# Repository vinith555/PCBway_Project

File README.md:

Custom PCB Badge for PCBWay Competition
Description
This badge PCB was designed for PCBWay’s competition, showcasing their precision in PCB manufacturing. It features integrated LEDs in a custom shape, making it ideal for use at events or as promotional giveaways. The badge is compact, durable, and powered by a battery or USB for easy use.

Features
Creative custom-shaped design
Integrated LEDs for visual appeal
Powered by a battery or USB for portability
Made from durable FR4 PCB material
Suitable for events, branding, or giveaways
Components
Material: FR4 PCB
LEDs: [Number of LEDs]
Power Source: Battery/USB
Other Components: Resistors, capacitors, etc.
PCB Specifications
Dimensions: [Specify dimensions]
Surface Finish: [e.g., HASL, ENIG]
Solder Mask Color: [e.g., Green, Red]
Layers: [Number of layers]
Getting Started
Requirements
Soldering tools
Battery or USB for power
Assembly Instructions
Solder the components (LEDs, resistors, etc.) to the PCB.
Connect the battery or USB power source.
Test the badge to ensure all components, especially the LEDs, are functioning properly.
Project Files
Gerber Files: [Provide link]
BOM: [Provide link]
Schematics: [Provide link]
License
Licensed under the [Insert License] License.

Contributing
Contributions are welcome! Submit pull requests or suggest improvements via the repository.

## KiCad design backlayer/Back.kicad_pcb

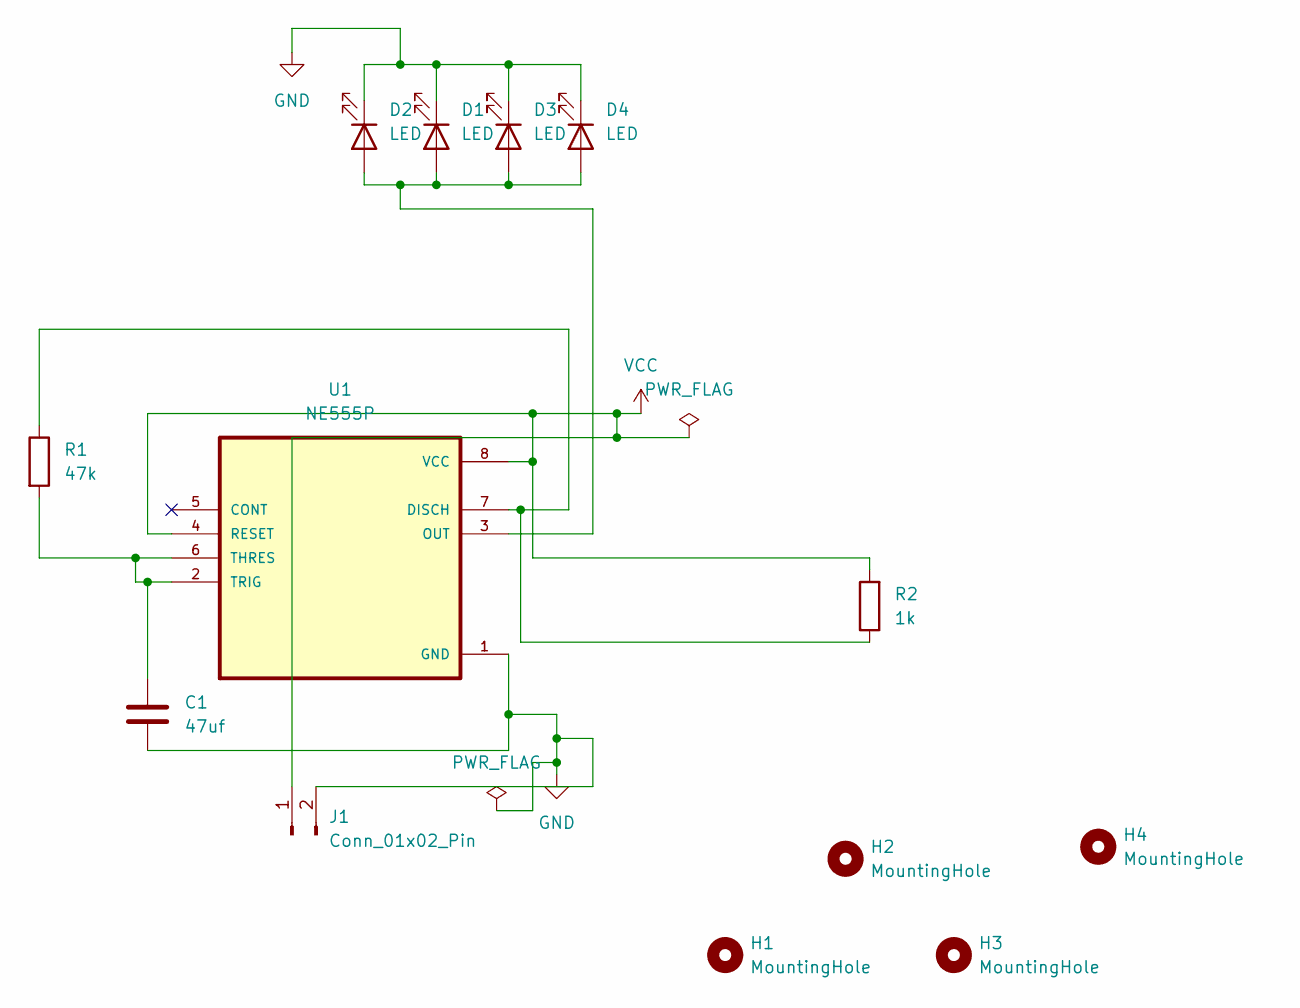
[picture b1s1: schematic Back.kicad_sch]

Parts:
C1: 47uf; CP_Radial_D12.5mm_P5.00mm
D1, D2, D3, D4: LED; LED_D3.0mm
H1, H2, H3, H4: MountingHole; MountingHole_2.5mm
J1: Conn_01x02_Pin; PinHeader_1x02_P2.54mm_Vertical
R1: 47k; R_Axial_DIN0207_L6.3mm_D2.5mm_P10.16mm_Horizontal
R2: 1k; R_Axial_DIN0207_L6.3mm_D2.5mm_P10.16mm_Horizontal
U1: NE555P; DIP794W45P254L959H508Q8

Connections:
GND: C1.2, D1.1 (K), D2.1 (K), D3.1 (K), D4.1 (K), J1.2, U1.1 (GND)
unnamed: D1.2 (A), D2.2 (A), D3.2 (A), D4.2 (A), U1.3 (OUT)
unnamed: R1.1, R2.1, U1.7 (DISCH)
unnamed: C1.1, R1.2, U1.2 (TRIG), U1.6 (THRES)
VCC: J1.1, R2.2, U1.4 (RESET), U1.8 (VCC)

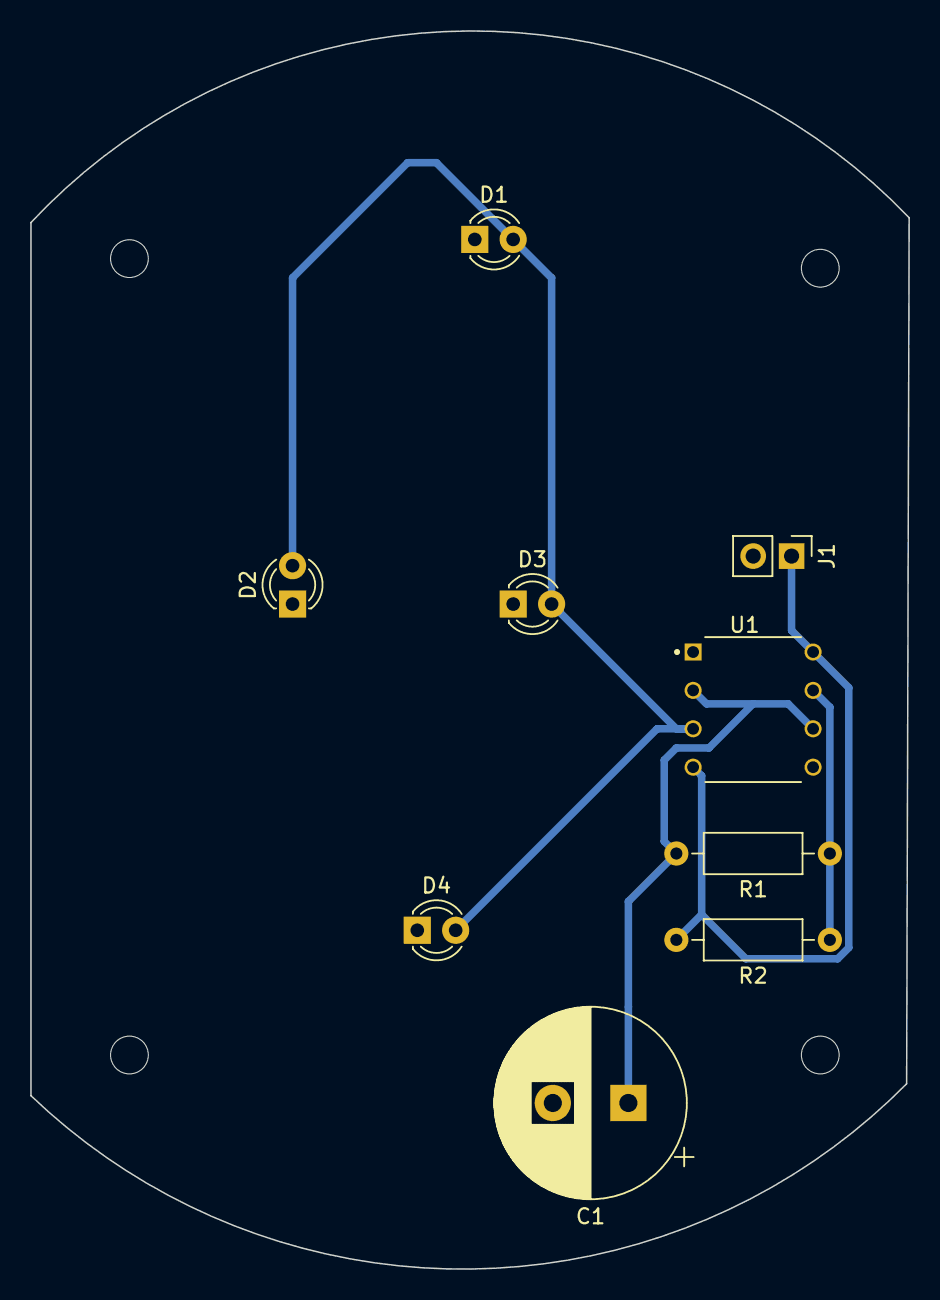
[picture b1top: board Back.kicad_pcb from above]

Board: 2 copper layers, 58.1 x 81.9 mm, 13 parts (0 on the bottom side), 5 nets.
